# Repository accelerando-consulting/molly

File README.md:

# Molly - an i2c keypad module

This is intended either to fit your existing microcontroller or be added to an off the
shelf microcontroller board to make  a standalone keypad (eg the TTGO T7-S3 is a good choice of board).

Theres some simple python code in here, but
you should probably consider the [ZMK firmware](https://github.com/zmkfirmware/zmk) as the best starting point.

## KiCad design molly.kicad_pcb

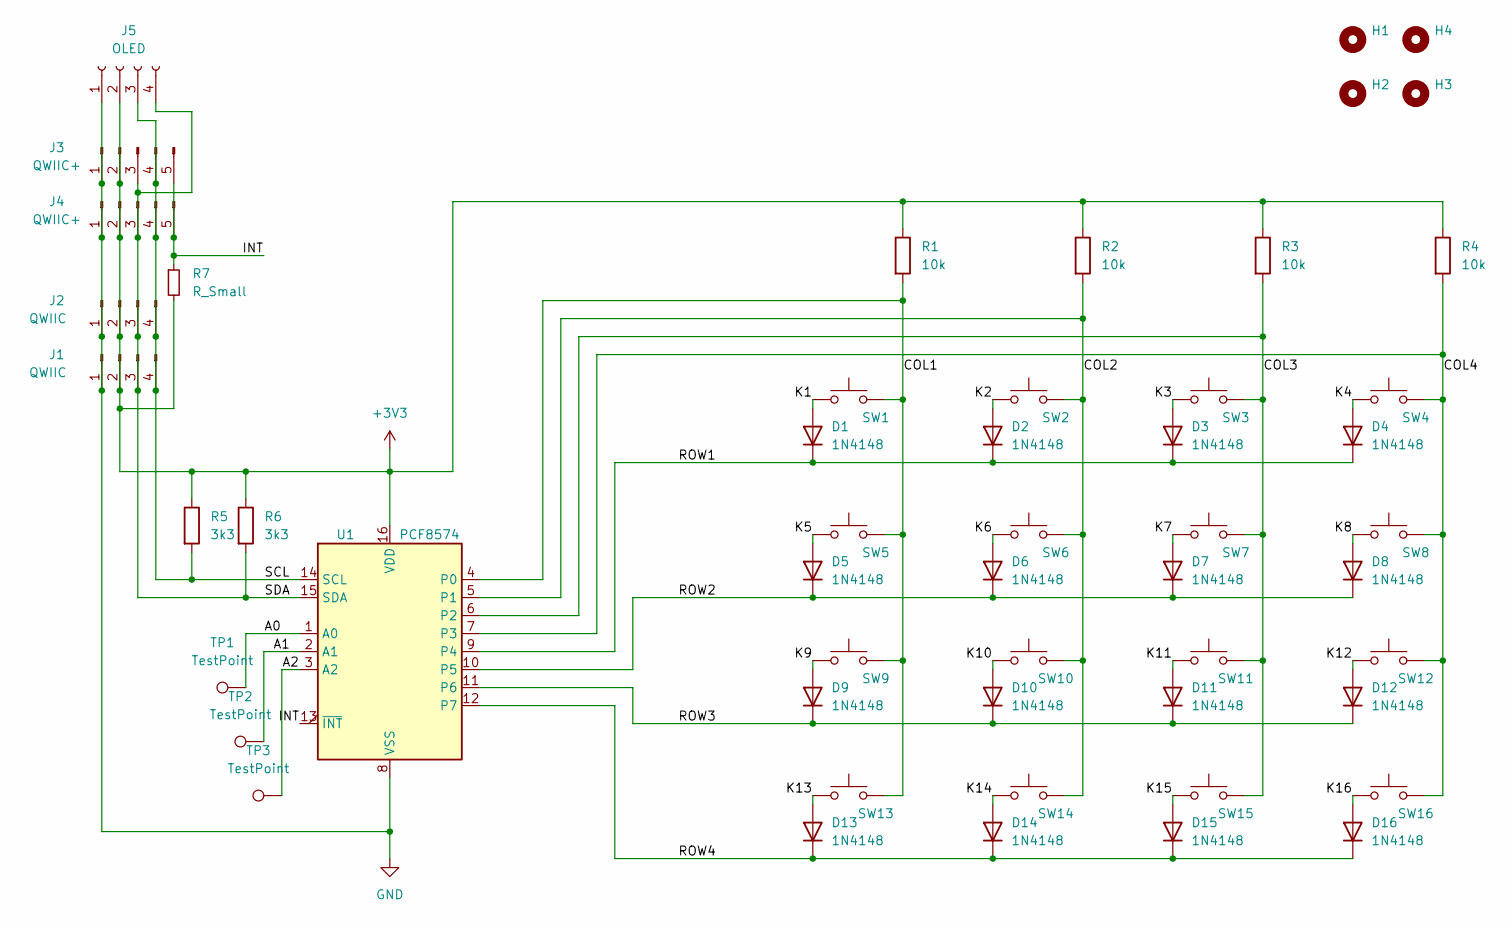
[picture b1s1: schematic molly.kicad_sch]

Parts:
D1, D2, D3, D4, D5, D6, D7, D8, D9, D10, D11, D12, D13, D14, D15, D16: 1N4148; D_0805_2012Metric
H1, H2, H3, H4: MountingHole; MountingHole_3.2mm_M3
J1, J2: QWIIC; JST_SH_BM04B-SRSS-TB_1x04-1MP_P1.00mm_Vertical
J3, J4: QWIIC+; JST_SH_BM05B-SRSS-TB_1x05-1MP_P1.00mm_Vertical
J5: OLED; PinSocket_1x04_P2.54mm_Vertical
R1, R2, R3, R4: 10k; R_0805_2012Metric
R5, R6: 3k3; R_0805_2012Metric
R7: R_Small; R_0805_2012Metric
SW1, SW2, SW3, SW4, SW5, SW6, SW7, SW8, SW9, SW10, SW11, SW12, SW13, SW14, SW15, SW16: Cherry MX; SW_PG1350
TP1, TP2, TP3: TestPoint; TestPoint_THTPad_2.0x2.0mm_Drill1.0mm
U1: PCF8574; SOIC-16W_7.5x10.3mm_P1.27mm

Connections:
+3V3: J1.2, J2.2, J3.2, J4.2, J5.2, R1.1, R2.1, R3.1, R4.1, R5.1, R6.1, R7.2, U1.16 (VDD)
/A0: TP1.1, U1.1 (A0)
/A1: TP2.1, U1.2 (A1)
/A2: TP3.1, U1.3 (A2)
/COL1: R1.2, SW1.2, SW5.2, SW9.2, SW13.2, U1.4 (P0)
/COL2: R2.2, SW2.2, SW6.2, SW10.2, SW14.2, U1.5 (P1)
/COL3: R3.2, SW3.2, SW7.2, SW11.2, SW15.2, U1.6 (P2)
/COL4: R4.2, SW4.2, SW8.2, SW12.2, SW16.2, U1.7 (P3)
/INT: J3.5, J4.5, R7.1, U1.13 (~INT)
/K1: D1.2 (A), SW1.1
/K2: D2.2 (A), SW2.1
/K3: D3.2 (A), SW3.1
/K4: D4.2 (A), SW4.1
/K5: D5.2 (A), SW5.1
/K6: D6.2 (A), SW6.1
/K7: D7.2 (A), SW7.1
/K8: D8.2 (A), SW8.1
/K9: D9.2 (A), SW9.1
/K10: D10.2 (A), SW10.1
/K11: D11.2 (A), SW11.1
/K12: D12.2 (A), SW12.1
/K13: D13.2 (A), SW13.1
/K14: D14.2 (A), SW14.1
/K15: D15.2 (A), SW15.1
/K16: D16.2 (A), SW16.1
/ROW1: D1.1 (K), D2.1 (K), D3.1 (K), D4.1 (K), U1.9 (P4)
/ROW2: D5.1 (K), D6.1 (K), D7.1 (K), D8.1 (K), U1.10 (P5)
/ROW3: D9.1 (K), D10.1 (K), D11.1 (K), D12.1 (K), U1.11 (P6)
/ROW4: D13.1 (K), D14.1 (K), D15.1 (K), D16.1 (K), U1.12 (P7)
/SCL: J1.4, J2.4, J3.4, J4.4, J5.3, R5.2, U1.14 (SCL)
/SDA: J1.3, J2.3, J3.3, J4.3, J5.4, R6.2, U1.15 (SDA)
GND: J1.1, J2.1, J3.1, J4.1, J5.1, U1.8 (VSS)

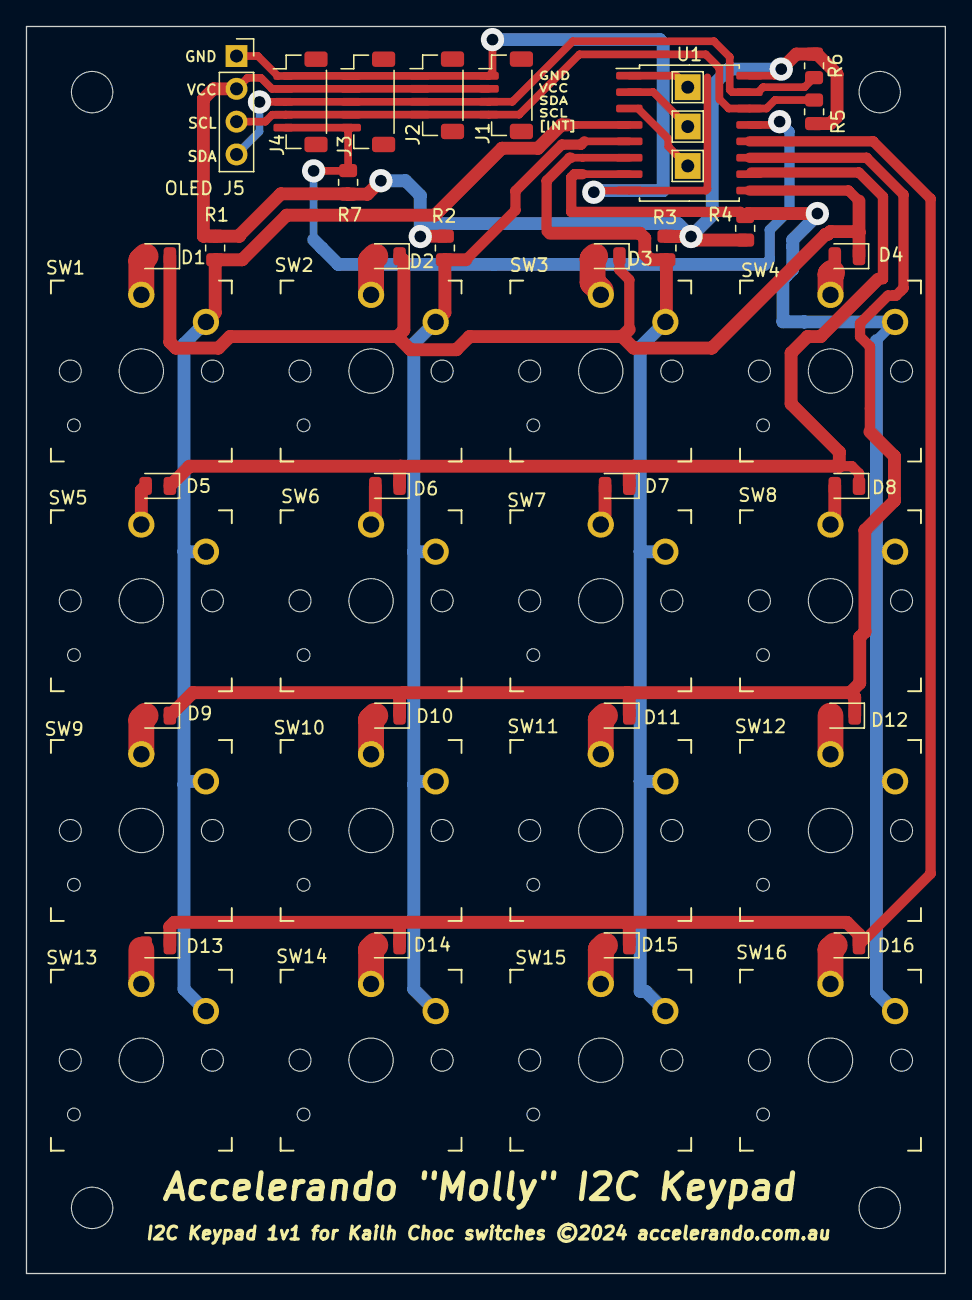
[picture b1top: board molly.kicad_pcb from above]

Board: 2 copper layers, 71.1 x 96.5 mm, 52 parts (0 on the bottom side), 32 nets.

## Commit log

2022-11-28 Molly v1, a 16 key i2c macropad
2026-06-30 Updated for more recent kicads, fix bassackwards screen pinout
2026-06-30 Add picture
2026-06-30 Update README.md
    remove reference to stacx, as I haven't pushed the molly module for stacx yet!

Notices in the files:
molly.kicad_pcb:
I2C Keypad 1v1 for Kailh Choc switches ©2024 accelerando.com.au
